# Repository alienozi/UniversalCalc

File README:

# Why?

We Love **Zwick**! This is a Student project on a self made Architecture (amateur!). It has an 8-Bit Bus.

## TODO List:
 
 - [ ] Arithmetic
	 - [X] Adder
	 - [ ] Subtracter 
	 - [ ] Multiplier
	 - [ ] Divider
	 - [ ] Square Root
##
 - [ ] Logic
	- [ ] Shift Left
	- [ ] Shift Right
	- [ ] Inverse
	- [ ] And
	- [ ] Or
	- [ ] Xor   
##
 - [ ] Compiler
	 - [ ] C
	 - [ ] Task1

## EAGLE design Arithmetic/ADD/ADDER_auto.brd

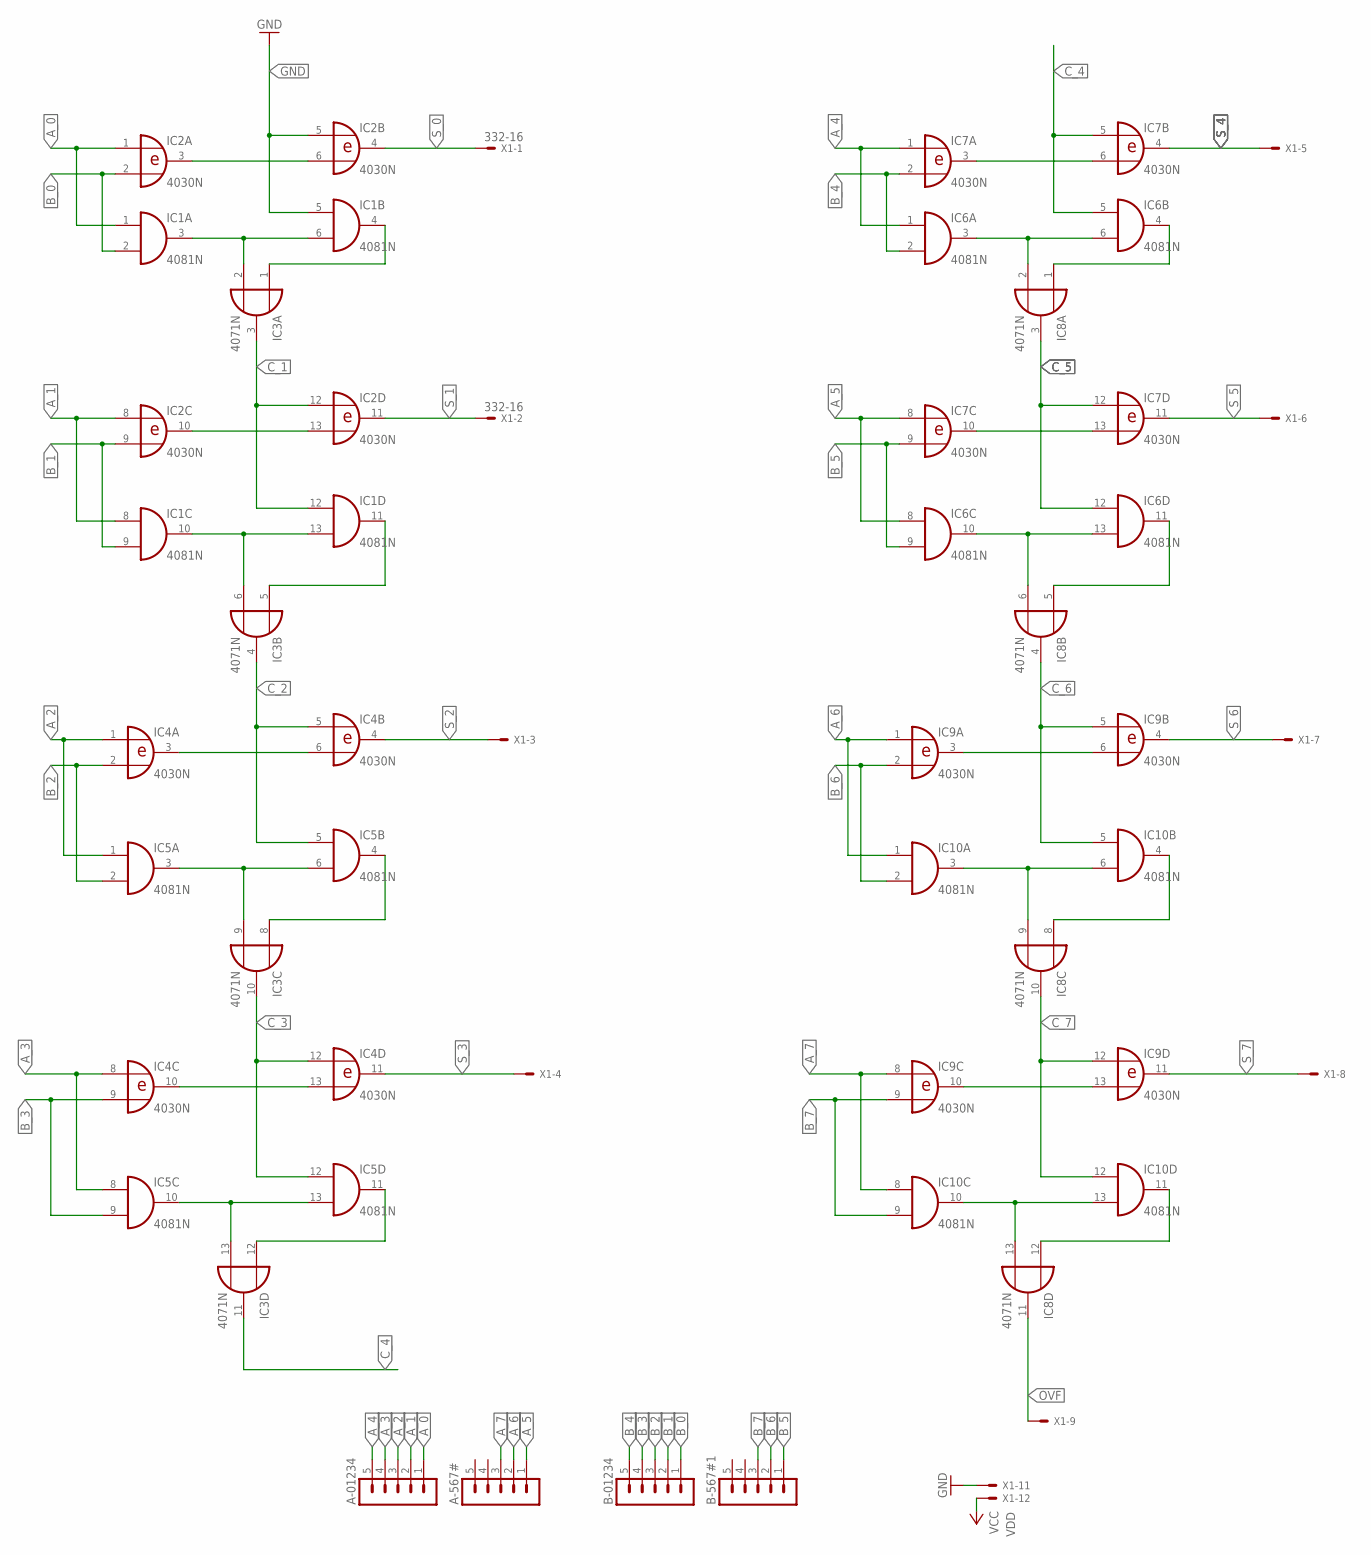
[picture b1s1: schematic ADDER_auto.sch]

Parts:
A-567#, A-01234: MA05-1
B-567#1, B-01234: MA05-1
IC1, IC5, IC6, IC10: 4081N; DIL14
IC2, IC4, IC7, IC9: 4030N; DIL14
IC3, IC8: 4071N; DIL14
X1: 332-16

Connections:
A_0: A-01234.1, IC1.1 (I0), IC2.1 (I0)
A_1: A-01234.2, IC1.8 (I0), IC2.8 (I0)
A_2: A-01234.3, IC4.1 (I0), IC5.1 (I0)
A_3: A-01234.4, IC4.8 (I0), IC5.8 (I0)
A_4: A-01234.5, IC6.1 (I0), IC7.1 (I0)
A_5: A-567#.1, IC6.8 (I0), IC7.8 (I0)
A_6: A-567#.2, IC9.1 (I0), IC10.1 (I0)
A_7: A-567#.3, IC9.8 (I0), IC10.8 (I0)
B_0: B-01234.1, IC1.2 (I1), IC2.2 (I1)
B_1: B-01234.2, IC1.9 (I1), IC2.9 (I1)
B_2: B-01234.3, IC4.2 (I1), IC5.2 (I1)
B_3: B-01234.4, IC4.9 (I1), IC5.9 (I1)
B_4: B-01234.5, IC6.2 (I1), IC7.2 (I1)
B_5: B-567#1.1, IC6.9 (I1), IC7.9 (I1)
B_6: B-567#1.2, IC9.2 (I1), IC10.2 (I1)
B_7: B-567#1.3, IC9.9 (I1), IC10.9 (I1)
C_1: IC1.12 (I0), IC2.12 (I0), IC3.3 (O)
C_2: IC3.4 (O), IC4.5 (I0), IC5.5 (I0)
C_3: IC3.10 (O), IC4.12 (I0), IC5.12 (I0)
C_4: IC3.11 (O), IC6.5 (I0), IC7.5 (I0)
C_5: IC6.12 (I0), IC7.12 (I0), IC8.3 (O)
C_6: IC8.4 (O), IC9.5 (I0), IC10.5 (I0)
C_7: IC8.10 (O), IC9.12 (I0), IC10.12 (I0)
GND: IC1.5 (I0), IC2.5 (I0), X1.11
unnamed: IC1.3 (O), IC1.6 (I1), IC3.2 (I1)
unnamed: IC1.4 (O), IC3.1 (I0)
unnamed: IC2.10 (O), IC2.13 (I1)
unnamed: IC4.3 (O), IC4.6 (I1)
unnamed: IC2.3 (O), IC2.6 (I1)
unnamed: IC1.10 (O), IC1.13 (I1), IC3.6 (I1)
unnamed: IC1.11 (O), IC3.5 (I0)
unnamed: IC3.13 (I1), IC5.10 (O), IC5.13 (I1)
unnamed: IC3.9 (I1), IC5.3 (O), IC5.6 (I1)
unnamed: IC6.3 (O), IC6.6 (I1), IC8.2 (I1)
unnamed: IC3.12 (I0), IC5.11 (O)
unnamed: IC4.10 (O), IC4.13 (I1)
unnamed: IC3.8 (I0), IC5.4 (O)
unnamed: IC6.4 (O), IC8.1 (I0)
unnamed: IC7.3 (O), IC7.6 (I1)
unnamed: IC7.10 (O), IC7.13 (I1)
unnamed: IC6.10 (O), IC6.13 (I1), IC8.6 (I1)
unnamed: IC6.11 (O), IC8.5 (I0)
unnamed: IC9.3 (O), IC9.6 (I1)
unnamed: IC8.9 (I1), IC10.3 (O), IC10.6 (I1)
unnamed: IC8.8 (I0), IC10.4 (O)
unnamed: IC8.13 (I1), IC10.10 (O), IC10.13 (I1)
unnamed: IC9.10 (O), IC9.13 (I1)
unnamed: IC8.12 (I0), IC10.11 (O)
OVF: IC8.11 (O), X1.9
S_0: IC2.4 (O), X1.1
S_1: IC2.11 (O), X1.2
S_2: IC4.4 (O), X1.3
S_3: IC4.11 (O), X1.4
S_4: IC7.4 (O), X1.5
S_5: IC7.11 (O), X1.6
S_6: IC9.4 (O), X1.7
S_7: IC9.11 (O), X1.8
VDD: IC1.14 (VDD), IC2.14 (VDD), IC3.14 (VDD), IC4.14 (VDD), IC5.14 (VDD), IC6.14 (VDD), IC7.14 (VDD), IC8.14 (VDD), IC9.14 (VDD), IC10.14 (VDD), X1.12
VSS: IC1.7 (VSS), IC2.7 (VSS), IC3.7 (VSS), IC4.7 (VSS), IC5.7 (VSS), IC6.7 (VSS), IC7.7 (VSS), IC8.7 (VSS), IC9.7 (VSS), IC10.7 (VSS)

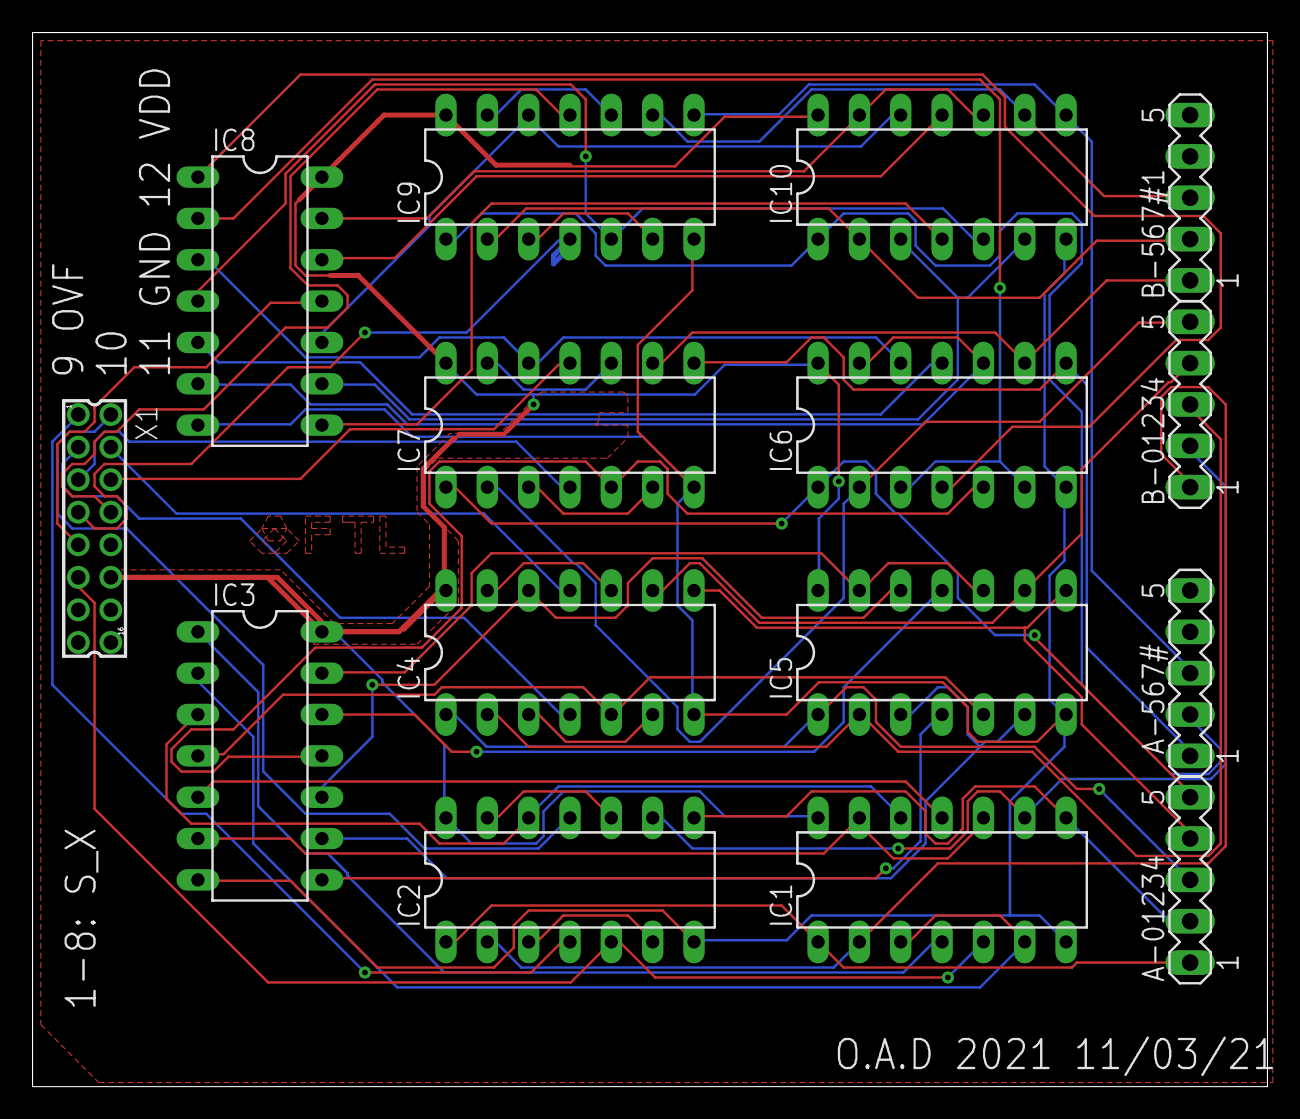
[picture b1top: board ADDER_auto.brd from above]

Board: 2 copper layers, 75.9 x 64.8 mm, 15 parts (0 on the bottom side), 59 nets.

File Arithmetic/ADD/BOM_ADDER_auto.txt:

Partlist exported from /home/kiwami/Documents/UniversalCalc/Arithmetic/ADD/ADDER_auto.sch at 21.03.21 01:36

Part    Value  Device Package Description           MF MPN OC_FARNELL OC_NEWARK POPULARITY
A-567#         MA05-1 MA05-1  PIN HEADER                   unknown    unknown   29        
A-01234        MA05-1 MA05-1  PIN HEADER                   unknown    unknown   29        
B-567#1        MA05-1 MA05-1  PIN HEADER                   unknown    unknown   29        
B-01234        MA05-1 MA05-1  PIN HEADER                   unknown    unknown   29        
IC1     4081N  4081N  DIL14   Quad 2-input AND                                  4         
IC2     4030N  4030N  DIL14   Quad XOR                                          0         
IC3     4071N  4071N  DIL14   Quad 2-input OR                                   0         
IC4     4030N  4030N  DIL14   Quad XOR                                          0         
IC5     4081N  4081N  DIL14   Quad 2-input AND                                  4         
IC6     4081N  4081N  DIL14   Quad 2-input AND                                  4         
IC7     4030N  4030N  DIL14   Quad XOR                                          0         
IC8     4071N  4071N  DIL14   Quad 2-input OR                                   0         
IC9     4030N  4030N  DIL14   Quad XOR                                          0         
IC10    4081N  4081N  DIL14   Quad 2-input AND                                  4         
X1      332-16 332-16 332-16  16 Pin - 2mm Dual Row                             0

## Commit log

2021-03-18 Added Readme
2021-03-18 ADDED FOLDERS
2021-03-18 Added Adder Circuit
2021-03-18 Added the Compiler (beta of beta lol)
2021-03-18 Rename README to README.md
2021-03-19 Edited Readme
2021-03-19 Gave Tasks
2021-03-20 Edited the C file
2021-03-20 Added Deadlines
2021-03-20 Added BOM for Adder
2021-03-22 MUL Started 0.1.2 Result
